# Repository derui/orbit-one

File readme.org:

* Orbit One
This is schematics for hand-made keyboard.

- Unified body, no split
- Modified Alice Layout
- 17mm key pitch
- Have 2 encoders side by side
- Installed glidepoint touch pad
- Acryl Gasket mount case

* PCB Data
This project uses kicad and PCB Data opened below.

- https://github.com/Salicylic-acid3/KiCAD_FootPrint

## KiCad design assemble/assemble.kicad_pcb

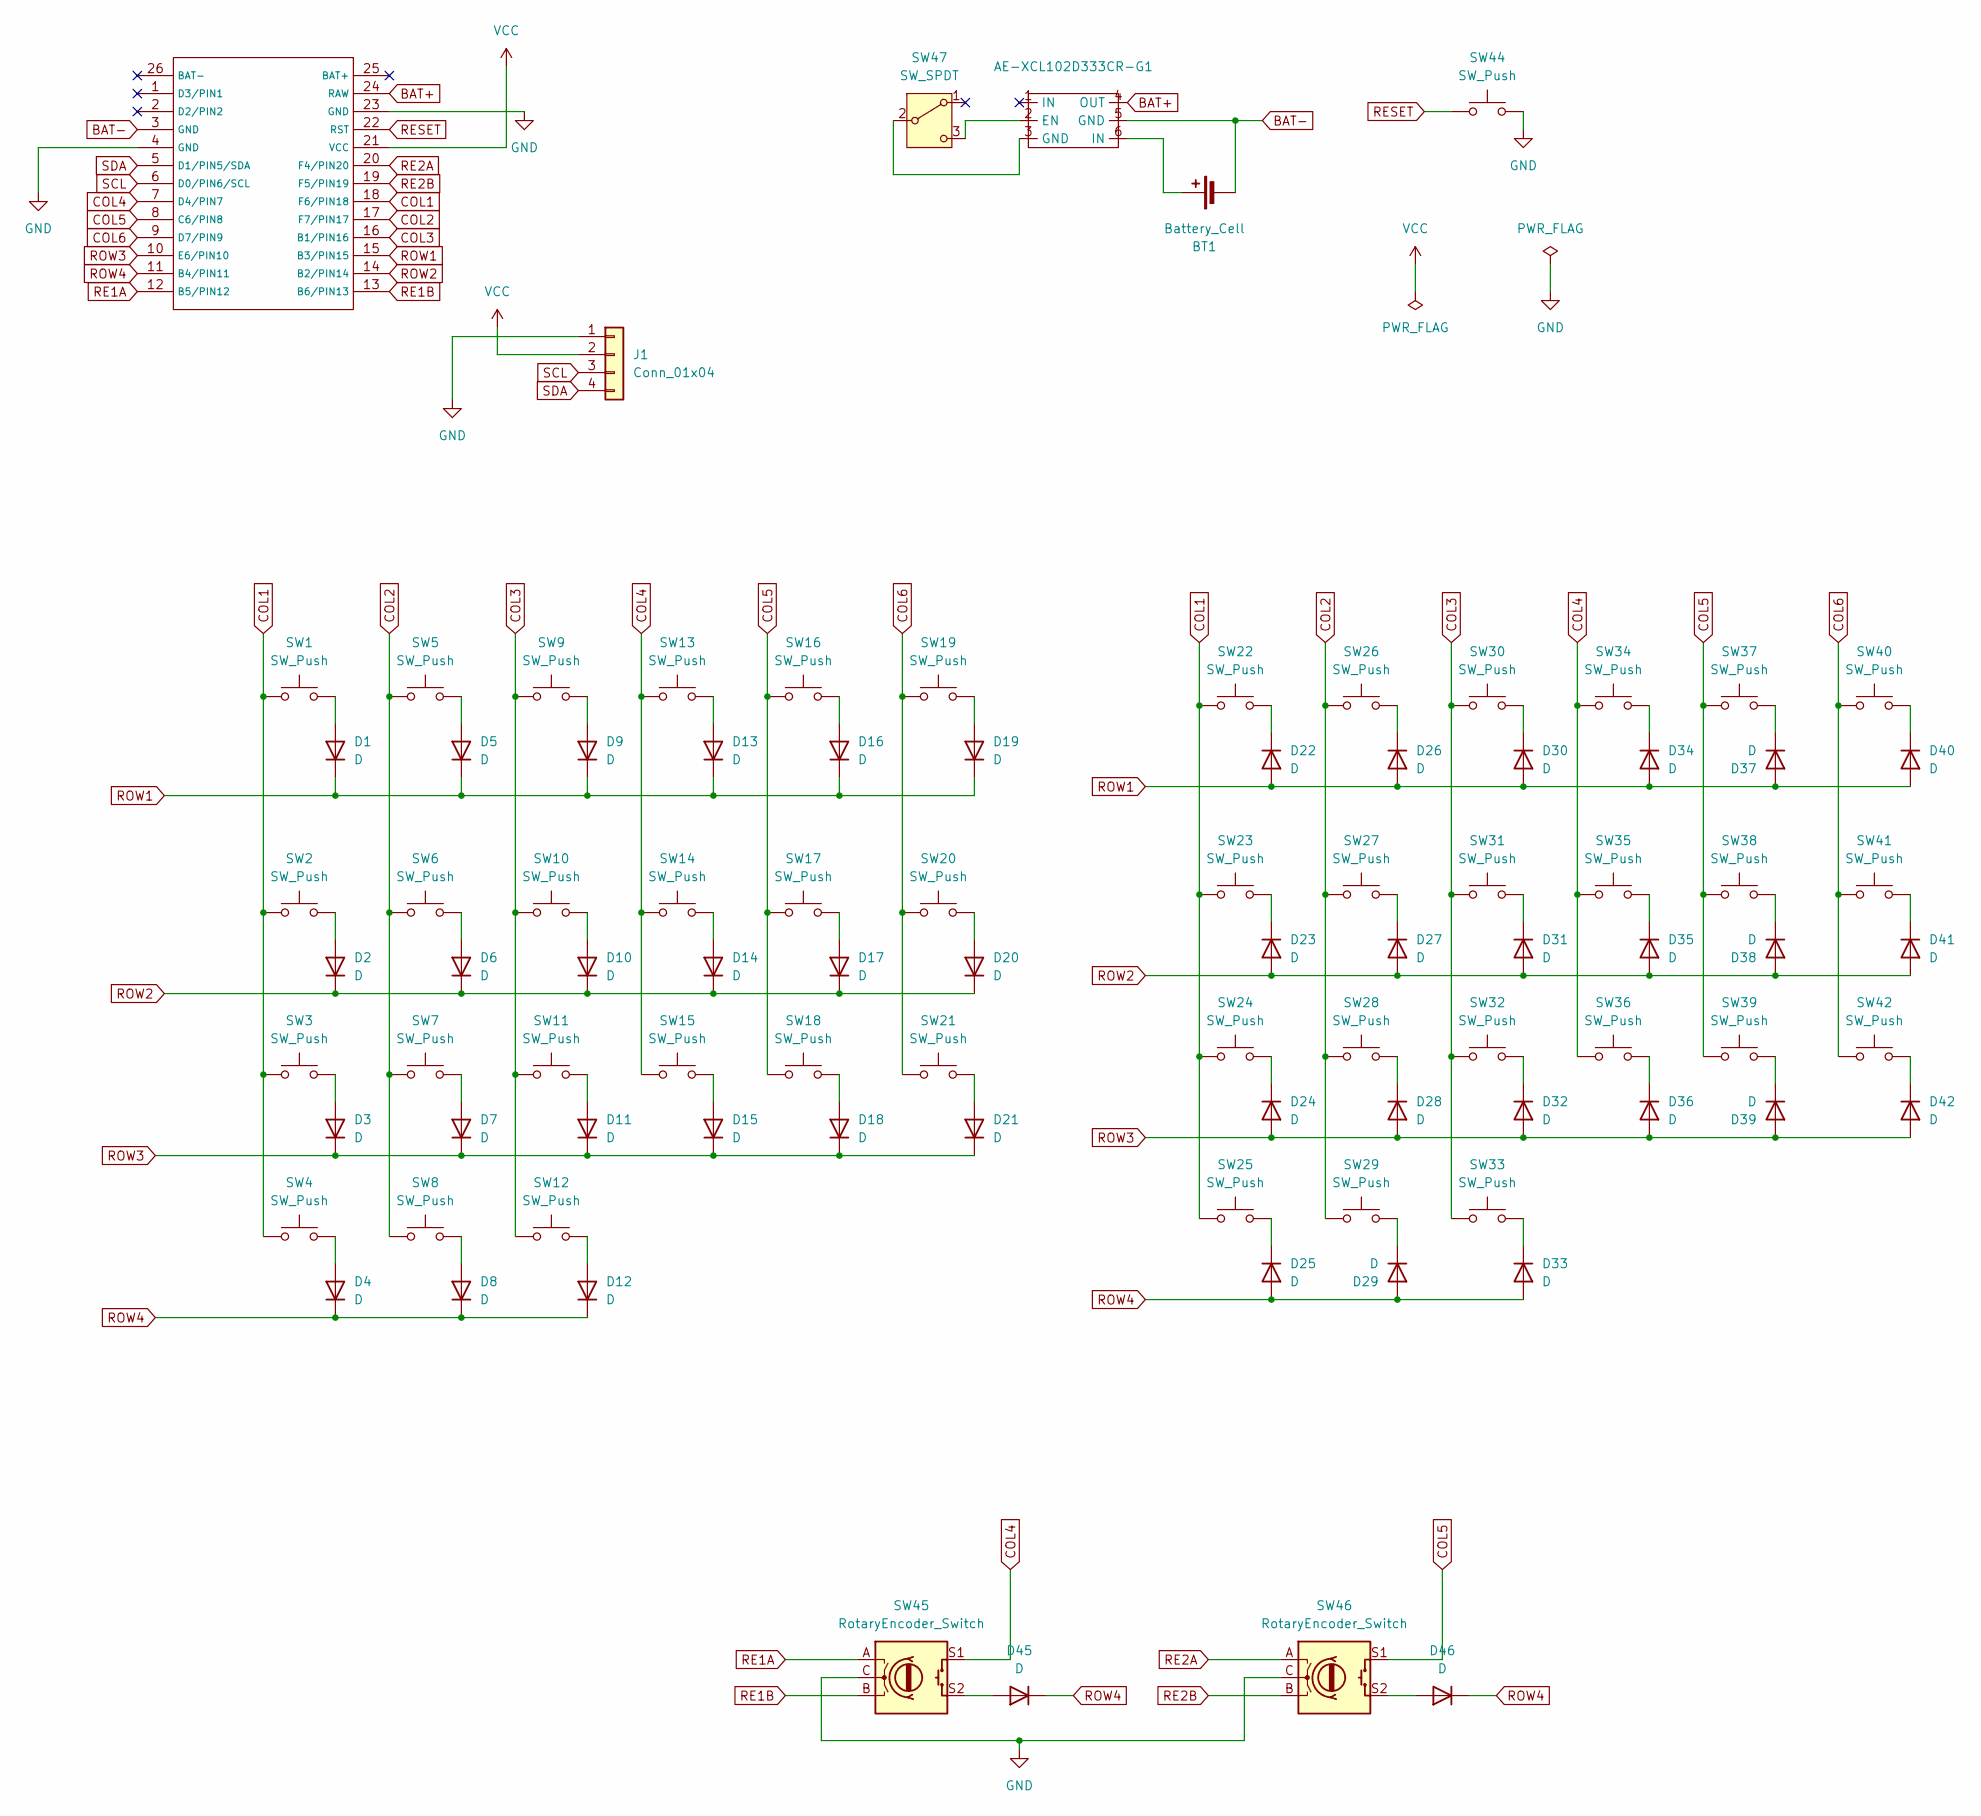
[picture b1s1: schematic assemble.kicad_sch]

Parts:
AE-XCL102D333CR-G1: AE-XCL102D333CR-G
BT1: Battery_Cell; Battery_AAA
D1, D2, D3, D4, D5, D6, D7, D8, D9, D10, D11, D12, D13, D14, D15, D16, D17, D18, D19, D20, D21, D22, D23, D24, D25, D26, D27, D28, D29, D30, D31, D32, D33, D34, D35, D36, D37, D38, D39, D40, D41, D42, D45, D46: D; Diode_TH_SMD
J1: Conn_01x04; PinSocket_1x04_P2.54mm_Vertical
SW1, SW2, SW3, SW4, SW5, SW6, SW7, SW8, SW9, SW10, SW11, SW12, SW13, SW14, SW15, SW16, SW17, SW18, SW19, SW20, SW21, SW22, SW23, SW24, SW25, SW26, SW27, SW28, SW29, SW30, SW31, SW32, SW33, SW34, SW35, SW36, SW37, SW38, SW39, SW40, SW41, SW42: SW_Push; CherryMX-HotSwap-1u_17
SW44: SW_Push; ResetSW
SW45, SW46: RotaryEncoder_Switch; RotaryEncoder_EC12E
SW47: SW_SPDT; TGSW_MSK-12D19
U1: Micon_BMP_7sKB

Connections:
BAT+: AE-XCL102D333CR-G1.4 (OUT), U1.24 (RAW)
BAT-: AE-XCL102D333CR-G1.5 (GND), BT1.2 (-), U1.3 (GND)
COL1: SW1.1, SW2.1, SW3.1, SW4.1, SW22.1, SW23.1, SW24.1, SW25.1, U1.18 (F6/PIN18)
COL2: SW5.1, SW6.1, SW7.1, SW8.1, SW26.1, SW27.1, SW28.1, SW29.1, U1.17 (F7/PIN17)
COL3: SW9.1, SW10.1, SW11.1, SW12.1, SW30.1, SW31.1, SW32.1, SW33.1, U1.16 (B1/PIN16)
COL4: SW13.1, SW14.1, SW15.1, SW34.1, SW35.1, SW36.1, SW45.S1, U1.7 (D4/PIN7)
COL5: SW16.1, SW17.1, SW18.1, SW37.1, SW38.1, SW39.1, SW46.S1, U1.8 (C6/PIN8)
COL6: SW19.1, SW20.1, SW21.1, SW40.1, SW41.1, SW42.1, U1.9 (D7/PIN9)
GND: J1.1, SW44.2, SW45.C, SW46.C, U1.4 (GND), U1.23 (GND)
unnamed: AE-XCL102D333CR-G1.2 (EN), SW47.3 (C)
unnamed: AE-XCL102D333CR-G1.6 (IN), BT1.1 (+)
unnamed: D1.2 (A), SW1.2
unnamed: D2.2 (A), SW2.2
unnamed: D3.2 (A), SW3.2
unnamed: D4.2 (A), SW4.2
unnamed: D5.2 (A), SW5.2
unnamed: D6.2 (A), SW6.2
unnamed: D7.2 (A), SW7.2
unnamed: D8.2 (A), SW8.2
unnamed: D9.2 (A), SW9.2
unnamed: D10.2 (A), SW10.2
unnamed: D11.2 (A), SW11.2
unnamed: D12.2 (A), SW12.2
unnamed: D13.2 (A), SW13.2
unnamed: D14.2 (A), SW14.2
unnamed: D15.2 (A), SW15.2
unnamed: D16.2 (A), SW16.2
unnamed: D17.2 (A), SW17.2
unnamed: D18.2 (A), SW18.2
unnamed: D19.2 (A), SW19.2
unnamed: D20.2 (A), SW20.2
unnamed: D21.2 (A), SW21.2
unnamed: D22.1 (K), SW22.2
unnamed: D23.1 (K), SW23.2
unnamed: D24.1 (K), SW24.2
unnamed: D25.1 (K), SW25.2
unnamed: D26.1 (K), SW26.2
unnamed: D27.1 (K), SW27.2
unnamed: D28.1 (K), SW28.2
unnamed: D29.1 (K), SW29.2
unnamed: D30.1 (K), SW30.2
unnamed: D31.1 (K), SW31.2
unnamed: D32.1 (K), SW32.2
unnamed: D33.1 (K), SW33.2
unnamed: D34.1 (K), SW34.2
unnamed: D35.1 (K), SW35.2
unnamed: D36.1 (K), SW36.2
unnamed: D37.1 (K), SW37.2
unnamed: D38.1 (K), SW38.2
unnamed: D39.1 (K), SW39.2
unnamed: D40.1 (K), SW40.2
unnamed: D41.1 (K), SW41.2
unnamed: D42.1 (K), SW42.2
unnamed: D45.2 (A), SW45.S2
unnamed: D46.2 (A), SW46.S2
unnamed: AE-XCL102D333CR-G1.3 (GND), SW47.2 (B)
RE1A: SW45.A, U1.12 (B5/PIN12)
RE1B: SW45.B, U1.13 (B6/PIN13)
RE2A: SW46.A, U1.20 (F4/PIN20)
RE2B: SW46.B, U1.19 (F5/PIN19)
RESET: SW44.1, U1.22 (RST)
ROW1: D1.1 (K), D5.1 (K), D9.1 (K), D13.1 (K), D16.1 (K), D19.1 (K), D22.2 (A), D26.2 (A), D30.2 (A), D34.2 (A), D37.2 (A), D40.2 (A), U1.15 (B3/PIN15)
ROW2: D2.1 (K), D6.1 (K), D10.1 (K), D14.1 (K), D17.1 (K), D20.1 (K), D23.2 (A), D27.2 (A), D31.2 (A), D35.2 (A), D38.2 (A), D41.2 (A), U1.14 (B2/PIN14)
ROW3: D3.1 (K), D7.1 (K), D11.1 (K), D15.1 (K), D18.1 (K), D21.1 (K), D24.2 (A), D28.2 (A), D32.2 (A), D36.2 (A), D39.2 (A), D42.2 (A), U1.10 (E6/PIN10)
ROW4: D4.1 (K), D8.1 (K), D12.1 (K), D25.2 (A), D29.2 (A), D33.2 (A), D45.1 (K), D46.1 (K), U1.11 (B4/PIN11)
SCL: J1.3, U1.6 (D0/PIN6/SCL); also elsewhere on the board
SDA: J1.4, U1.5 (D1/PIN5/SDA); also elsewhere on the board
VCC: J1.2, U1.21 (VCC); also elsewhere on the board

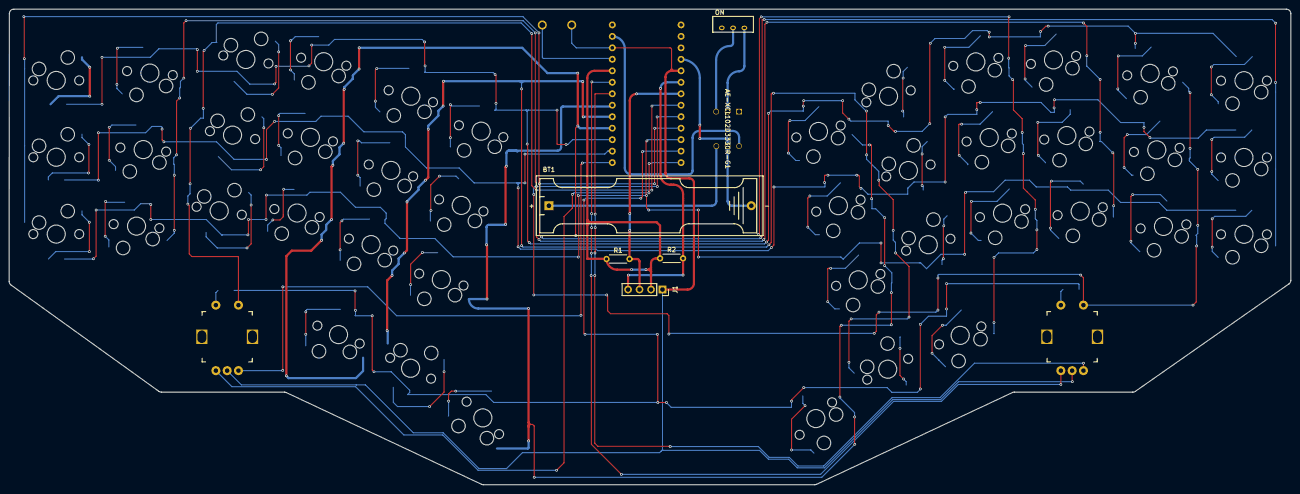
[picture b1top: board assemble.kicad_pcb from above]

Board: 2 copper layers, 283.6 x 105.3 mm, 96 parts (1 on the bottom side), 68 nets.

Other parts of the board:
R1, R2: R_470k; R_Axial_DIN0204_L3.6mm_D1.6mm_P5.08mm_Horizontal

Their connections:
SCL: R1.2; also elsewhere on the board
SDA: R2.2; also elsewhere on the board
VCC: R1.1, R2.1; also elsewhere on the board

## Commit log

2025-05-17 feat: setup env
2025-05-17 feat: add schematic
2025-05-18 feat: add pcb data
2025-05-18 feat: re-annotation
2025-05-18 fix: orientations
2025-05-18 feat: add edge cut
2025-05-19 fix: typo
2025-05-25 feat: add switch plate
2025-05-29 feat: change screw
2025-05-31 feat: wiring
2025-05-31 fix: screw point
2025-05-31 fix: footprint
2025-06-06 [ci skip] docs: read me
2025-06-07 feat: add bottom form
2025-06-15 fix: invalid I2C connection
2025-06-22 feat: add v2
2025-06-26 feat: implement v2 pcb
2025-06-28 fix: plot setting
